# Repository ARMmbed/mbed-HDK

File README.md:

## This repository is not actively maintained anymore. For the latest updates, please visit: https://github.com/ARMmbed/mbed-HDK-Eagle-Projects

# mbed-HDK

The mbed Hardware Development Kit (mbed-HDK) is a collection of hardware design resources built on top of **Eagle PCB** that have been gathered to assist in the development of custom hardware benefiting from the mbed ecosystem, such as mbed OS, mbed SDK and associated technologies such as DAPLink. Working with development boards that were based on the mbed HDK is the most efficient way to get started with the mbed platform.

## Benefits of mbed-HDK

The mbed-HDK provides:

* Extensive collection of Eagle CAD parts libraries.
* Production Design Projects
	* Proven and manufactured mbed platforms for your reference complete with:
		* Eagle Schematic and Board files
		* PDF Schematic and Board copies
		* CAM Job GERBERS for manufacture (including pick/place and drill)
		* BOM (Bill of Materials)
* Bare Design Projects
	* Modular reference blocks of mbed TARGET and INTERFACE chip allowing rapid prototyping complete with:
		* Eagle Schematic and Board files
		* PDF Schematic copies

Please keep in mind that the resources are provided "as is". Though best efforts have been made to ensure the highest possible quality, no support or guarantees can be offered. The latest versions of Production Designs contained in the mbed HDK have been successfully manufactured by a third-party manufacturer and proven to work.

## Getting Started - Setup

The [User Guide](Docs/USER-GUIDE.md) will walk you through the setup to get the most out of the mbed-HDK.

## Getting Started - Your first PCB design
With the mbed-HDK the goal is to allow rapid PCB CAD prototyping for mbed designs, therefore we provide designs to get you started as quickly as possible. There are multiple ways to create your first design.
	
* Starting with a [Production Design Project](https://github.com/ARMmbed/mbed-HDK/tree/master/Production%20Design%20Projects/)
	* Choose this option if you wish to take an existing design that has been manufactured and tested as a starting point, or to make minor changes and then release yourself.

* Starting with a [Bare Design Project](Docs/DESIGN-GUIDE.md)
	* Choose this option if you wish to rapid prototype a design using modular blocks that have already been developed, these modular blocks include DAPLink INTERFACES and mbed TARGETS. For a simple guide to see how this works and how much time it will save.

* Starting with a blank Schematic and Board
	* Choose this option if you wish to utilise only the mbed-HDK tools in your design, this will still allow quick prototyping of mbed designs through using due to the provided mbed-hdk lbr, dru, ulp and CAM

## Moving On - Contributing your parts and designs

If you wish to contribute to the mbed HDK you can do so.

The [Contributors Guide](Docs/CONTRIBUTORS-GUIDE.md) details on how to contribute back to the mbed-HDK. There are 3 possible ways to contribute back to the mbed-HDK.

1. Contributing to mbed-HDK Eagle Libraries
2. Contributing to mbed-HDK Production Design Projects
3. Contributing to mbed-HDK Bare Design Projects

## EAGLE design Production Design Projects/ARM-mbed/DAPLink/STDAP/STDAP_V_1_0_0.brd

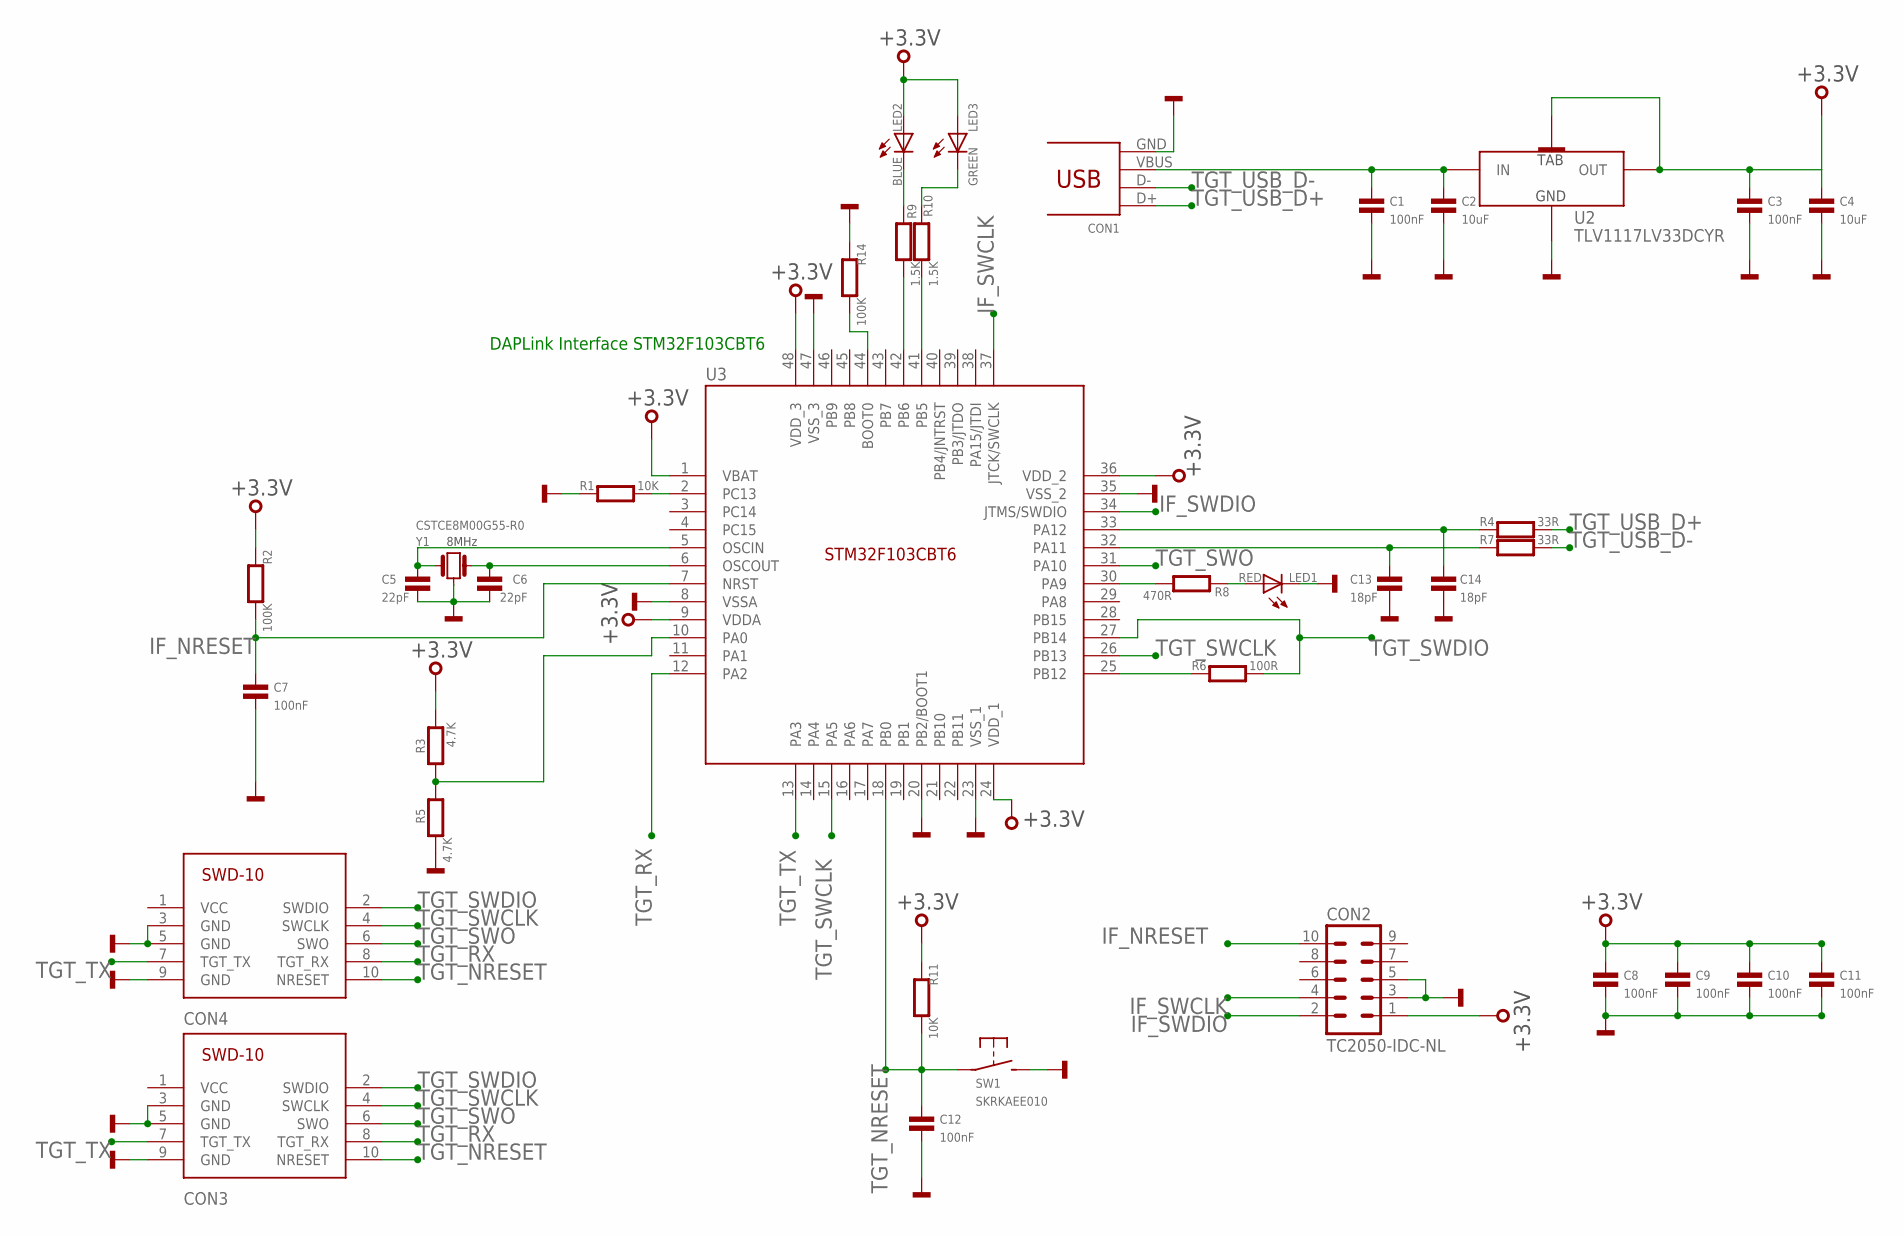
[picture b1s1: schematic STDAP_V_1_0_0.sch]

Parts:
C1, C3, C7, C8, C9, C10, C11, C12: 100nF; 0402
C2, C4: 10uF; 0603
C5, C6: 22pF; 0402
C13, C14: 18pF; 0402
CON1: 47346-0001; USB-MICRO-B-H
CON2: TC2050-IDC-NL
CON3: 3020-10-0200-00
CON4: 3220-10-0200-00
LED1: RED; CHIPLED_0603
LED2: BLUE; CHIPLED_0603
LED3: GREEN; CHIPLED_0603
R1, R11: 10K; 0402
R2, R14: 100K; 0402
R3, R5: 4.7K; 0402
R4, R7: 33R; 0402
R6: 100R; 0402
R8: 470R; 0402
R9, R10: 1.5K; 0402
SW1: SKRKAEE010
U2: TLV1117LV33DCYR; SOT223
U3: STM32F103CBT6; LQFP48
Y1: CSTCE8M00G55-R0

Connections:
+3.3V: C3.1, C4.1, C8.1, C9.1, C10.1, C11.1, CON2.1, LED2.A, LED3.A, R2.1, R3.1, R11.1, U2.OUT(1) (OUT), U2.OUT(2) (TAB), U3.1 (VBAT), U3.9 (VDDA), U3.24 (VDD_1), U3.36 (VDD_2), U3.48 (VDD_3)
GND: C1.2, C2.2, C3.2, C4.2, C5.2, C6.2, C7.2, C8.2, C9.2, C10.2, C11.2, C12.2, C13.2, C14.2, CON1.GND, CON2.3, CON2.5, CON3.3 (GND), CON3.5 (GND), CON3.9 (GND), CON4.3 (GND), CON4.5 (GND), CON4.9 (GND), LED1.C, R1.1, R5.2, R14.1, SW1.P$2 (S), U2.GND, U3.8 (VSSA), U3.20 (PB2/BOOT1), U3.23 (VSS_1), U3.35 (VSS_2), U3.47 (VSS_3), Y1.2
IF_NRESET: C7.1, CON2.10, R2.2, U3.7 (NRST)
IF_SWCLK: CON2.4, U3.37 (JTCK/SWCLK)
IF_SWDIO: CON2.2, U3.34 (JTMS/SWDIO)
unnamed: C1.1, C2.1, CON1.VBUS, U2.IN
unnamed: R8.2, U3.30 (PA9)
unnamed: R14.2, U3.44 (BOOT0)
unnamed: R1.2, U3.2 (PC13)
unnamed: C6.1, U3.6 (OSCOUT), Y1.3
unnamed: C5.1, U3.5 (OSCIN), Y1.1
unnamed: R3.2, R5.1, U3.10 (PA0)
unnamed: R9.2, U3.42 (PB6)
unnamed: R10.2, U3.41 (PB5)
unnamed: LED1.A, R8.1
unnamed: R6.1, U3.25 (PB12)
unnamed: LED2.C, R9.1
unnamed: LED3.C, R10.1
unnamed: C14.1, R4.1, U3.33 (PA12)
unnamed: C13.1, R7.1, U3.32 (PA11)
TGT_NRESET: C12.1, CON3.10 (NRESET), CON4.10 (NRESET), R11.2, SW1.P$1, U3.18 (PB0)
TGT_RX: CON3.8 (TGT_RX), CON4.8 (TGT_RX), U3.12 (PA2)
TGT_SWCLK: CON3.4 (SWCLK), CON4.4 (SWCLK), U3.15 (PA5), U3.26 (PB13)
TGT_SWDIO: CON3.2 (SWDIO), CON4.2 (SWDIO), R6.2, U3.27 (PB14)
TGT_SWO: CON3.6 (SWO), CON4.6 (SWO), U3.31 (PA10)
TGT_TX: CON3.7 (TGT_TX), CON4.7 (TGT_TX), U3.13 (PA3)
TGT_USB_D+: CON1.D+, R4.2
TGT_USB_D-: CON1.D-, R7.2

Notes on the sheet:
8MHz
DAPLink Interface STM32F103CBT6

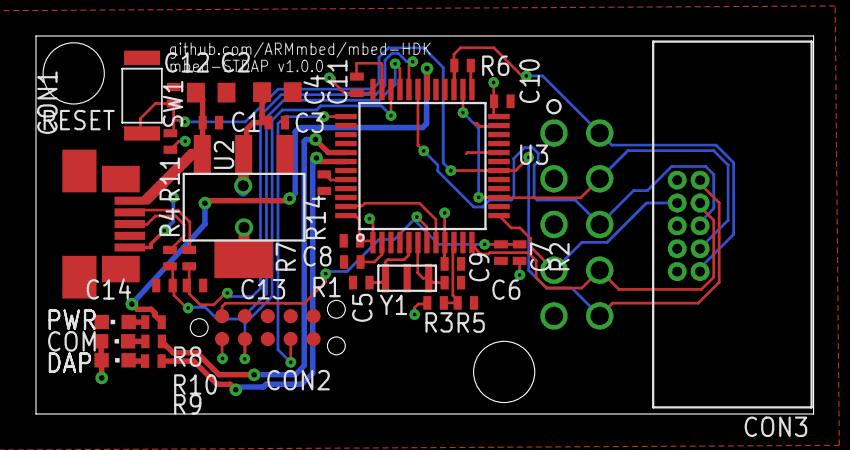
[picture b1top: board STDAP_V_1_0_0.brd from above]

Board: 2 copper layers, 43.2 x 21.0 mm, 37 parts (1 on the bottom side), 28 nets.

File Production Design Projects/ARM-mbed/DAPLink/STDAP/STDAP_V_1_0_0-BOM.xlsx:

Qty | Value | Device | Package | Parts | Description | MF | MFN | OC-DIGIKEY | OC-MOUSER | OC-NEWARK
1 | 3020-10-0200-00 | 3020-10-0200-00 | 3020-10-0200-00 | CON3 | 10 Positions Header Connector 0.100 (2.54mm) Through Hole | CNC Tech | 3020-10-0200-00 | 1175-1615-ND
1 | 3220-10-0200-00 | 3220-10-0200-00 | 3220-10-0200-00 | CON4 | 10 Positions Header Connector 0.050 (1.27mm) Through Hole | CNC Tech | 3220-10-0200-00 | 1175-1628-ND
2 | 1.5K | RESISTOR0402 | 402 | R9, R10 | Resistor | Panasonic | ERJ-2RKF1501X | P1.50KLCT-ND | 667-ERJ-2RKF1501X | 2302656
2 | 100K | RESISTOR0402 | 402 | R2, R14 | Resistor | Vishay | CRCW0402100KJNED | 541-100KJCT-ND | 71-CRCW0402J-100K-E3 | 1652738
1 | 100R | RESISTOR0402 | 402 | R6 | Resistor | Bourns | CR0402-JW-101GLF | CR0402-JW-101GLFCT-ND | 652-CR0402JW-101GLF | 32K2112
8 | 100nF | CAPACITOR0402 | 402 | C1, C3, C7, C8, C9, C10, C11, C12 | Capacitor | AVX | 0402YD104KAT2A | 478-1126-1-ND | 581-0402YD104K | 1327666
2 | 10K | RESISTOR0402 | 402 | R1, R11 | Resistor | Vishay | CRCW040210K0JNED | 541-10KJCT-ND | 71-CRCW0402J-10K-E3 | 59M6696
2 | 10uF | CAPACITOR0603 | 603 | C2, C4 | Capacitor | Yageo | CC0603MRX5R5BB106 | 311-1448-1-ND | 603-CC603MRX5R5BB106 | 1458902
2 | 18pF | CAPACITOR0402 | 402 | C13, C14 | Capacitor | Vishay | CRCW0402470RJNED | 541-470JCT-ND | 71-CRCW0402J-470-E3 | 59M6737
2 | 22pF | CAPACITOR0402 | 402 | C5, C6 | Capacitor | AVX | 04025A220JAT2A | 478-1074-1-ND | 581-04025A220J | 1327634
2 | 33R | RESISTOR0402 | 402 | R4, R7 | Resistor | Vishay | CRCW040233R0JNED | 541-33JCT-ND | 71-CRCW0402J-33-E3 | 72M6782
2 | 4.7K | RESISTOR0402 | 402 | R3, R5 | Resistor | Panasonic | ERJ-2RKF4701X | P4.70KLCT-ND | 667-ERJ-2RKF4701X | 64R5288
1 | 470R | RESISTOR0402 | 402 | R8 | Resistor | Vishay | CRCW0402470RJNED | 541-470JCT-ND | 71-CRCW0402J-470-E3 | 59M6737
1 | 47346-0001 | 47346-0001 | USB-MICRO-B-H | CON1 | USB Receptacle Horizontal Micro Type B | MOLEX | 47346-0001 |  | 538-47346-0001 | 1568026
1 | BLUE | SMD_LED0603 | CHIPLED_0603 | LED2 | LED SMD, Colour Blue | Wurth Electronics Inc | 150060BS75000 | 732-4966-1-ND | 710-150060BS75000 | 2322069
1 | CSTCE8M00G55-R0 | CSTCE8M00G55-R0 | CSTCE8M00G55-R0 | Y1 | Resonator Cermanic, Murata 8MHz 33pF | Murata | CSTCE8M00G55-R0 | 490-1195-1-ND | 81-CSTCE8M00G55-R0 | 2443270
1 | GREEN | SMD_LED0603 | CHIPLED_0603 | LED3 | LED SMD, Colour Green | Wurth Electronics Inc | 150060GS75000 | 732-4971-1-ND | 710-150060GS75000 | 2322070
1 | RED | SMD_LED0603 | CHIPLED_0603 | LED1 | LED SMD, Colour Red | Wurth Electronics Inc | 150060RS75000 | 732-4978-1-ND | 710-150060RS75000 | 2322071
1 | SKRKAEE010 | SKRKAEE010 | SKRKAEE010 | SW1 | MOMENTARY SWITCH PUSH VERTICAL (SPST) | ALPS | SKRKAEE010 |  | 688-SKRKAE
1 | STM32F103CBT6 | STM32F103CBT6 | LQFP48 | U3 | ARM¬Æ Cortex¬Æ-M3 STM32 F1 Microcontroller IC 32-Bit 72MHz 128KB (128K x 8) FLA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 | STMicroelectronics | STM32F103CBT6 | 497-6288-ND | 511-STM32F103CBT6 | 11N8296
1 | TLV1117LV33DCYR | TLV1117LV33DCYR | SOT223 | U2 | LDO Fixed Regulator 3.3v, 1A | Texas Instruments | TLV1117LV33DCYR | 296-28778-1-ND | 595-TLV1117LV33DCYR | 2323647

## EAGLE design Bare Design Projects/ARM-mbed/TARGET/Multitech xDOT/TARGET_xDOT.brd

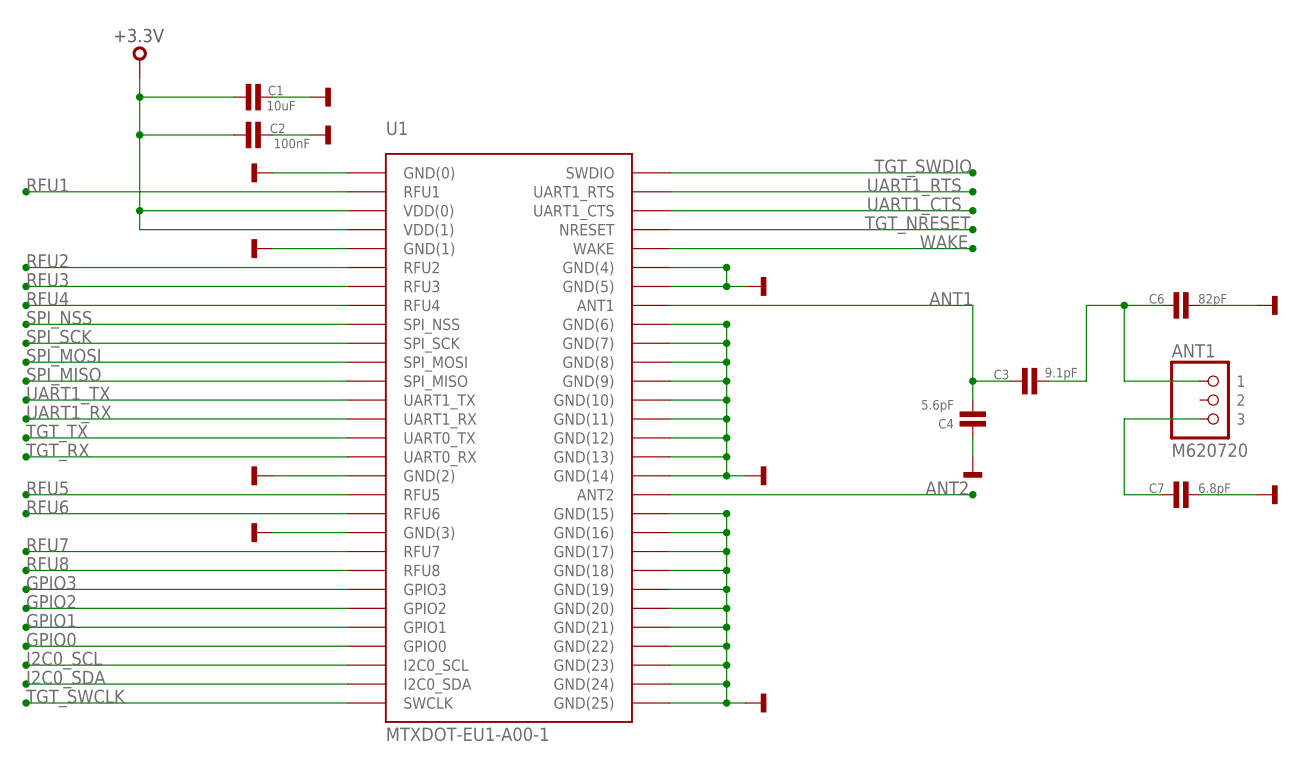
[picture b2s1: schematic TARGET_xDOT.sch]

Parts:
ANT1: M620720
C1: 10uF; 0603
C2: 100nF; 0603
C3: 9.1pF; 0402
C4: 5.6pF; 0402
C6: 82pF; 0402
C7: 6.8pF; 0402
U1: MTXDOT-EU1-A00-1; MTXDOT-EU1/NA1-A00-1

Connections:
+3.3V: C1.1, C2.1, U1.P$3 (VDD(0)), U1.P$4 (VDD(1))
ANT1: C3.1, C4.2, U1.P$37 (ANT1)
ANT2: U1.P$47 (ANT2)
GND: C1.2, C2.2, C4.1, C6.1, C7.1, U1.P$1 (GND(0)), U1.P$5 (GND(1)), U1.P$17 (GND(2)), U1.P$20 (GND(3)), U1.P$35 (GND(4)), U1.P$36 (GND(5)), U1.P$38 (GND(6)), U1.P$39 (GND(7)), U1.P$40 (GND(8)), U1.P$41 (GND(9)), U1.P$42 (GND(10)), U1.P$43 (GND(11)), U1.P$44 (GND(12)), U1.P$45 (GND(13)), U1.P$46 (GND(14)), U1.P$48 (GND(15)), U1.P$49 (GND(16)), U1.P$50 (GND(17)), U1.P$51 (GND(18)), U1.P$52 (GND(19)), U1.P$53 (GND(20)), U1.P$54 (GND(21)), U1.P$55 (GND(22)), U1.P$56 (GND(23)), U1.P$57 (GND(24)), U1.P$58 (GND(25))
GPIO0: U1.P$26 (GPIO0)
GPIO1: U1.P$25 (GPIO1)
GPIO2: U1.P$24 (GPIO2)
GPIO3: U1.P$23 (GPIO3)
I2C0_SCL: U1.P$27 (I2C0_SCL)
I2C0_SDA: U1.P$28 (I2C0_SDA)
unnamed: ANT1.P$3 (3), C7.2
unnamed: ANT1.P$1 (1), C3.2, C6.2
RFU1: U1.P$2 (RFU1)
RFU2: U1.P$6 (RFU2)
RFU3: U1.P$7 (RFU3)
RFU4: U1.P$8 (RFU4)
RFU5: U1.P$18 (RFU5)
RFU6: U1.P$19 (RFU6)
RFU7: U1.P$21 (RFU7)
RFU8: U1.P$22 (RFU8)
SPI_MISO: U1.P$12 (SPI_MISO)
SPI_MOSI: U1.P$11 (SPI_MOSI)
SPI_NSS: U1.P$9 (SPI_NSS)
SPI_SCK: U1.P$10 (SPI_SCK)
TGT_NRESET: U1.P$33 (NRESET)
TGT_RX: U1.P$16 (UART0_RX)
TGT_SWCLK: U1.P$29 (SWCLK)
TGT_SWDIO: U1.P$30 (SWDIO)
TGT_TX: U1.P$15 (UART0_TX)
UART1_CTS: U1.P$32 (UART1_CTS)
UART1_RTS: U1.P$31 (UART1_RTS)
UART1_RX: U1.P$14 (UART1_RX)
UART1_TX: U1.P$13 (UART1_TX)
WAKE: U1.P$34 (WAKE)

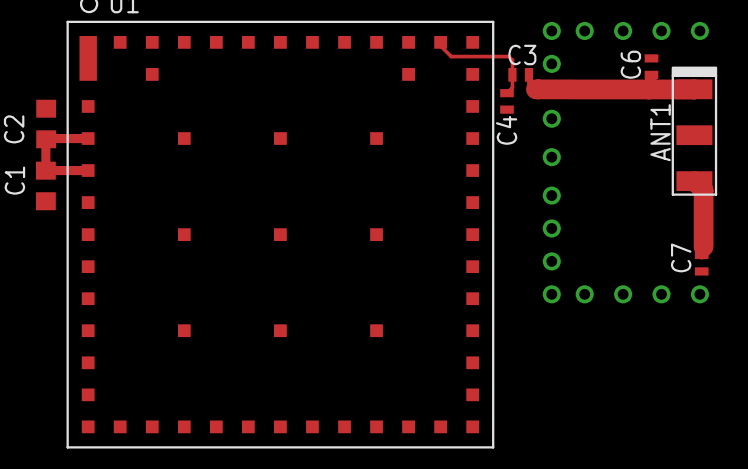
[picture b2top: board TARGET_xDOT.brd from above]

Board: 2 copper layers, 8 parts (0 on the bottom side), 5 nets.

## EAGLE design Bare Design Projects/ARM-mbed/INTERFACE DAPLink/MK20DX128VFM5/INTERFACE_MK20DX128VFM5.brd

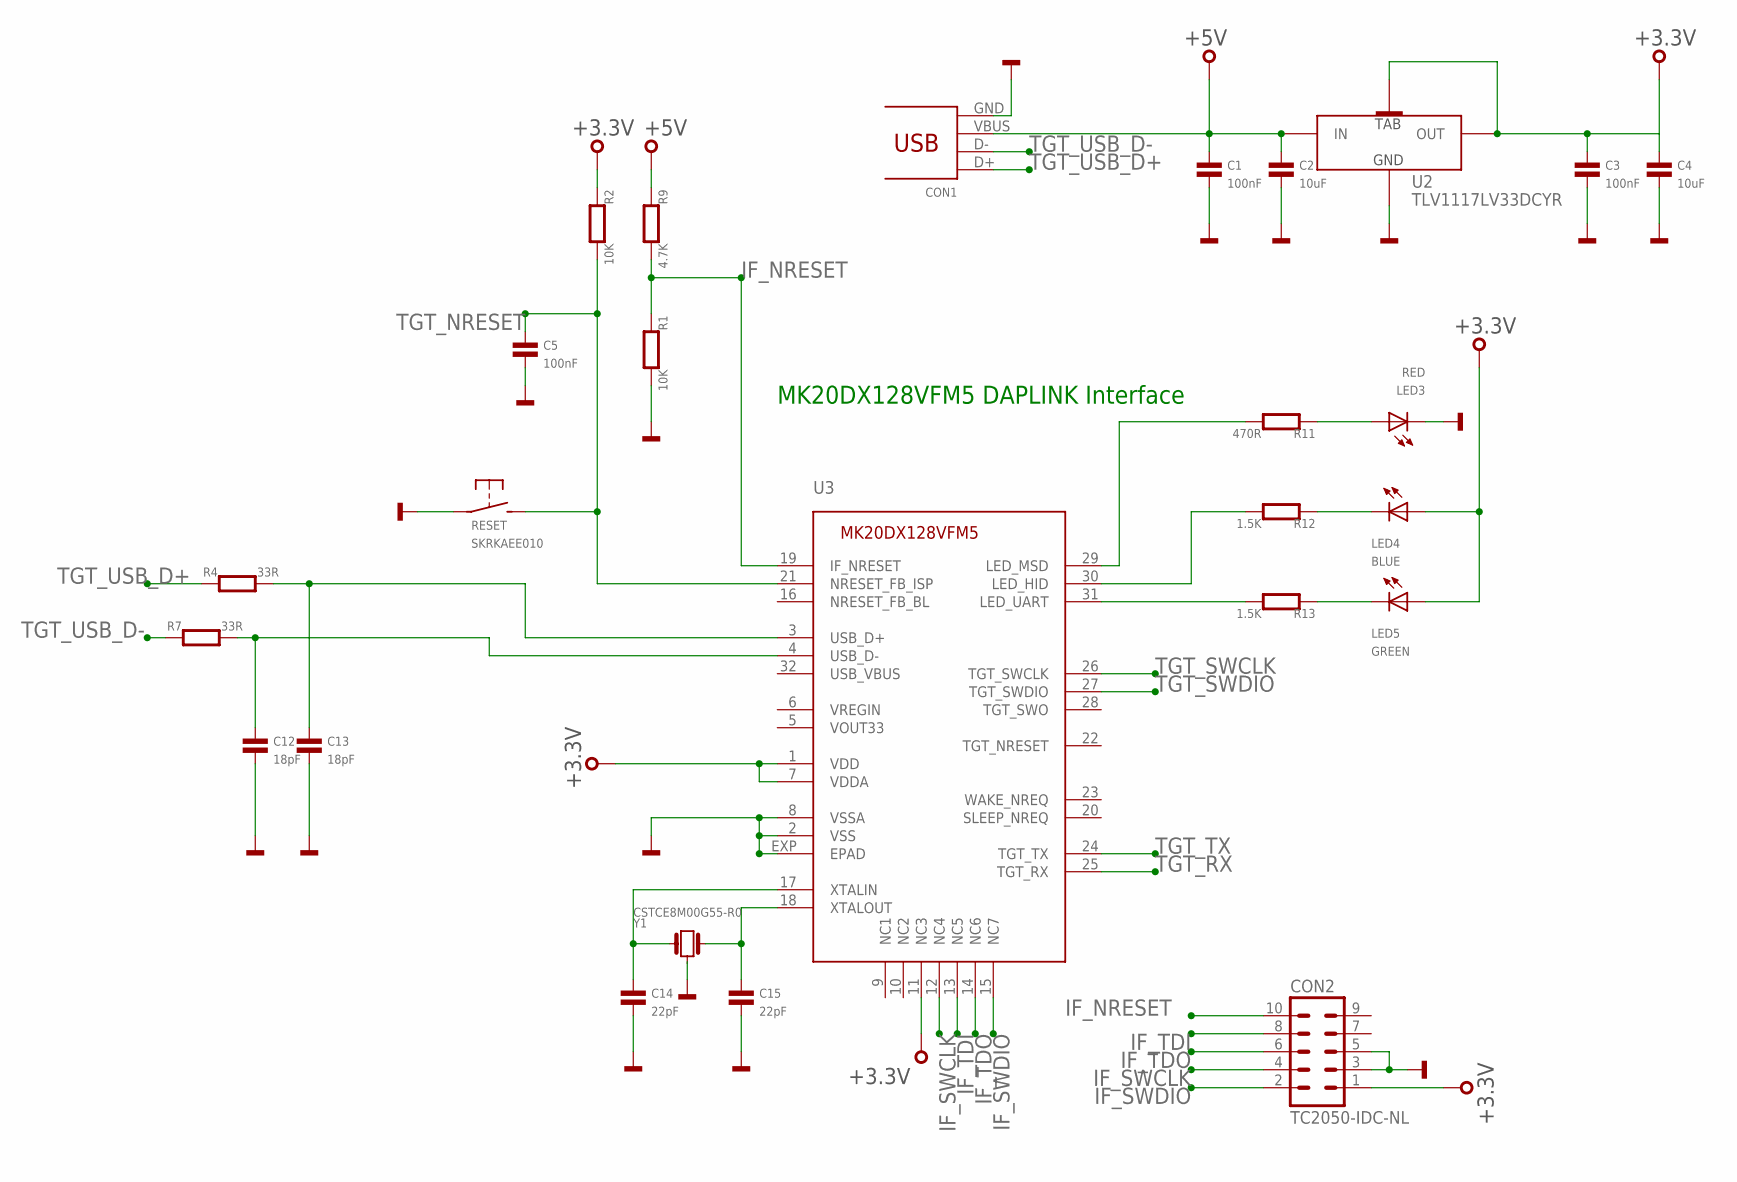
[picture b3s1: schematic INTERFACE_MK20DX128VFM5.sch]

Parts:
C1, C3, C5: 100nF; 0402
C2, C4: 10uF; 0603
C12, C13: 18pF; 0402
C14, C15: 22pF; 0402
CON1: 47346-0001; USB-MICRO-B-H
CON2: TC2050-IDC-NL
LED3: RED; CHIPLED_0603
LED4: BLUE; CHIPLED_0603
LED5: GREEN; CHIPLED_0603
R1, R2: 10K; 0402
R4, R7: 33R; 0402
R9: 4.7K; 0402
R11: 470R; 0402
R12, R13: 1.5K; 0402
RESET: SKRKAEE010
U2: TLV1117LV33DCYR; SOT223
U3: IF_MK20DX128VFM5; HVQFN33
Y1: CSTCE8M00G55-R0

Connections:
+3.3V: C3.1, C4.1, CON2.1, LED4.A, LED5.A, R2.1, U2.OUT(1) (OUT), U2.OUT(2) (TAB), U3.1 (VDD), U3.7 (VDDA), U3.11 (NC3)
+5V: C1.1, C2.1, CON1.VBUS, R9.1, U2.IN
GND: C1.2, C2.2, C3.2, C4.2, C5.2, C12.2, C13.2, C14.2, C15.2, CON1.GND, CON2.3, CON2.5, LED3.C, R1.2, RESET.P$1, U2.GND, U3.2 (VSS), U3.8 (VSSA), U3.EXP (EPAD), Y1.2
HID: R12.2, U3.30 (LED_HID)
IF_NRESET: CON2.10, R1.1, R9.2, U3.19 (IF_NRESET)
IF_SWCLK: CON2.4, U3.12 (NC4)
IF_SWDIO: CON2.2, U3.15 (NC7)
IF_TDI: CON2.8, U3.13 (NC5)
IF_TDO: CON2.6, U3.14 (NC6)
MSD: R11.2, U3.29 (LED_MSD)
unnamed: LED3.A, R11.1
unnamed: C13.1, R4.2, U3.3 (USB_D+)
unnamed: C12.1, R7.2, U3.4 (USB_D-)
unnamed: LED4.C, R12.1
unnamed: LED5.C, R13.1
unnamed: C15.1, U3.18 (XTALOUT), Y1.3
unnamed: C14.1, U3.17 (XTALIN), Y1.1
TGT_NRESET: C5.1, R2.2, RESET.P$2 (S), U3.21 (NRESET_FB_ISP)
TGT_RX: U3.25 (TGT_RX)
TGT_SWCLK: U3.26 (TGT_SWCLK)
TGT_SWDIO: U3.27 (TGT_SWDIO)
TGT_TX: U3.24 (TGT_TX)
TGT_USB_D+: CON1.D+, R4.1
TGT_USB_D-: CON1.D-, R7.1
UART: R13.2, U3.31 (LED_UART)

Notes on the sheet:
MK20DX128VFM5 DAPLINK Interface

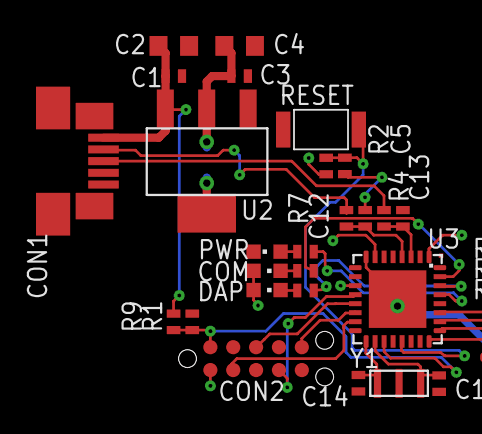
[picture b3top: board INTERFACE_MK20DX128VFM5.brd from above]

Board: 2 copper layers, 26 parts (0 on the bottom side), 21 nets.

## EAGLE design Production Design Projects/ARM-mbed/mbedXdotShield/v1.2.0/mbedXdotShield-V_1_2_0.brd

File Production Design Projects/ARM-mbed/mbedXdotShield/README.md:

## mbedXdotShield

The mbed xDOT shield features a Multitech xDOT LORA module, with mbed compatabile drag-drop programming. This device is both a independent platform or can act as a shield to make any device send or recieve LORA data via UART.

## Whats included here?

* Eagle Schematic and Board files
* PDF Schematic and Board copies
* CAM Job GERBERS for manufacture (including pick/place and drill)
* BOM (Bill of Materials)
* eBOM (An online BOM for easy purchasing!)

The design features:

        1. Multitech xDOT module: ST ARM® Cortex® M3 processor (STM32L151CCU6)
        2. DAPLink Interface LPC11u35: Drag Drop programming
        3. 868/915MHz LoRa chip antenna
        4. AT45DB161E-SSHD-T Serial Flash
        5. 3V JST-PH Battery connector
        6. Arduino style headers: Allowing device to operate as LoRa shield
        7. UART swap: Slide switch, allowing UART TX/RX to be swapped, if using as shield switch to 'On'

## Hardware

The hardware design files can be found in this repo as part of the mbed HDK and are referenced by their most up-to-date version v’x.x.x’.(If you wish to find an older project version, navigate to releases or checkout a previous commit).

## Software and more info

The software for tests and more info can be found in the [CI Test Shield github repository](http://www.github.com/armmbed/ci-test-shield). 

## How to get hardware

1. Buy pre-assembled board from vendor (todo)
2. Do it yourself

## Revisions
- **v 1.2.0** (23/06/17)
	-  'D2' Replaced with 'R29' 0ohm.
	-  mbed enabled logo on silkscreen
	-  Modified 'CON2' now recommended voltage is 4.5V (from 3V) for VBAT, rerouted to input of LDO 'U2'
- **v 1.1.0** (01/06/17)
	- 	'R3':1.5K->220R
	-  'R13','R14':470R->1.5K
	-  Placed resistors 'R14'-to-'R27' on front of PCB (no components on rear)
	-  Rerouted UART1TX, UART1RX (improved antenna performance)
	-  Moved USB micro further into board
- **v 1.0.0** (18/05/17)
 - Initial Commit

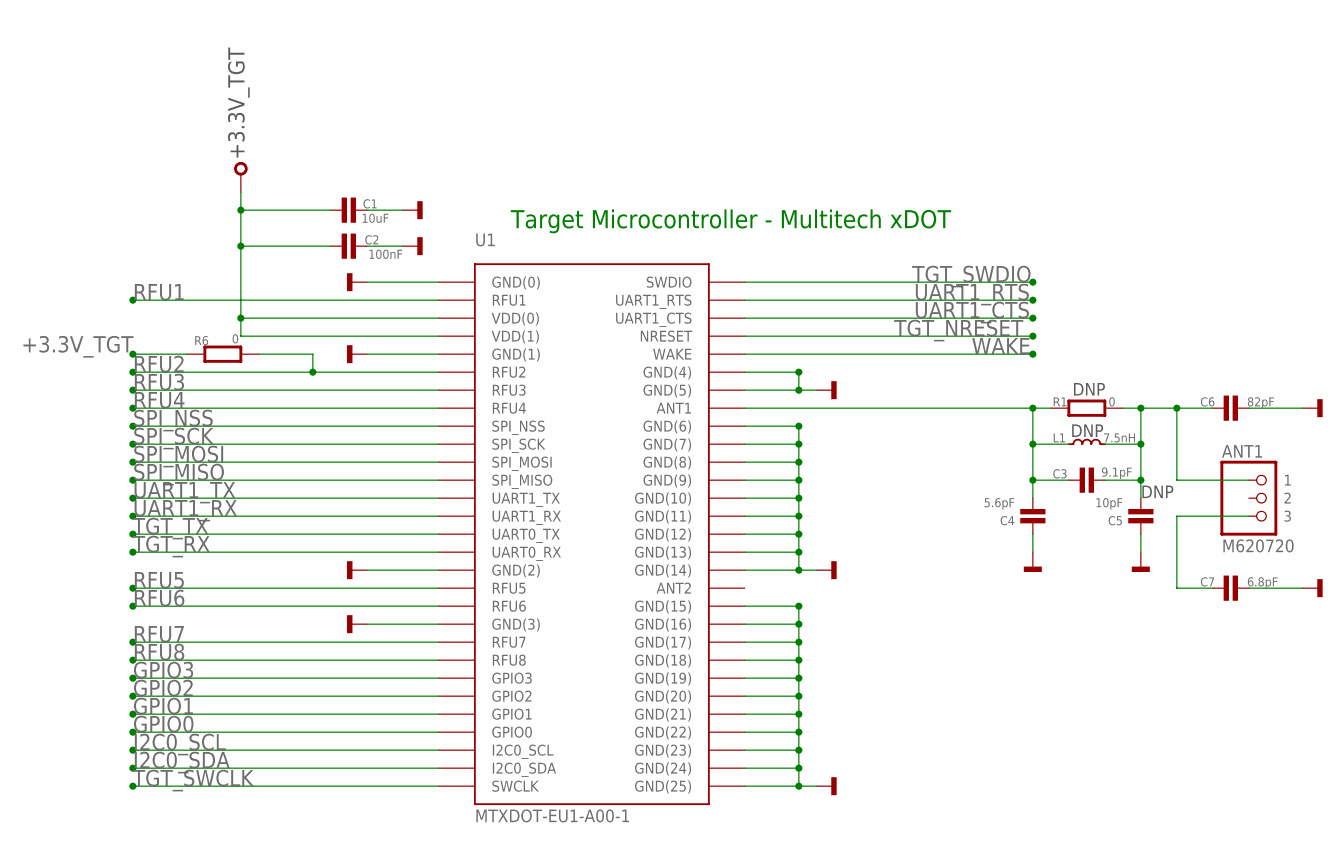
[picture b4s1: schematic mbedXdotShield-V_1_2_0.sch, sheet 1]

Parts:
ANT1: M620720
C1: 10uF; 0603
C2: 100nF; 0603
C3: 9.1pF; 0402
C4: 5.6pF; 0402
C5: 10pF; 0402
C6: 82pF; 0402
C7: 6.8pF; 0402
L1: 7.5nH; 0402
R1, R6: 0; 0402
U1: MTXDOT-EU1-A00-1; MTXDOT-EU1/NA1-A00-1

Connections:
+3.3V_TGT: C1.1, C2.1, R6.1, U1.P$3 (VDD(0)), U1.P$4 (VDD(1)); also elsewhere on the board
ANT1: C3.1, C4.2, L1.1, R1.1, U1.P$37 (ANT1)
GND: C1.2, C2.2, C4.1, C5.1, C6.1, C7.1, U1.P$1 (GND(0)), U1.P$5 (GND(1)), U1.P$17 (GND(2)), U1.P$20 (GND(3)), U1.P$35 (GND(4)), U1.P$36 (GND(5)), U1.P$38 (GND(6)), U1.P$39 (GND(7)), U1.P$40 (GND(8)), U1.P$41 (GND(9)), U1.P$42 (GND(10)), U1.P$43 (GND(11)), U1.P$44 (GND(12)), U1.P$45 (GND(13)), U1.P$46 (GND(14)), U1.P$48 (GND(15)), U1.P$49 (GND(16)), U1.P$50 (GND(17)), U1.P$51 (GND(18)), U1.P$52 (GND(19)), U1.P$53 (GND(20)), U1.P$54 (GND(21)), U1.P$55 (GND(22)), U1.P$56 (GND(23)), U1.P$57 (GND(24)), U1.P$58 (GND(25)); also elsewhere on the board
GPIO0: U1.P$26 (GPIO0); also elsewhere on the board
GPIO1: U1.P$25 (GPIO1); also elsewhere on the board
GPIO2: U1.P$24 (GPIO2); also elsewhere on the board
GPIO3: U1.P$23 (GPIO3); also elsewhere on the board
I2C0_SCL: U1.P$27 (I2C0_SCL); also elsewhere on the board
I2C0_SDA: U1.P$28 (I2C0_SDA); also elsewhere on the board
unnamed: ANT1.P$3 (3), C7.2
unnamed: ANT1.P$1 (1), C3.2, C5.2, C6.2, L1.2, R1.2
RFU1: U1.P$2 (RFU1)
RFU2: R6.2, U1.P$6 (RFU2)
RFU3: U1.P$7 (RFU3)
RFU4: U1.P$8 (RFU4)
RFU5: U1.P$18 (RFU5)
RFU6: U1.P$19 (RFU6)
RFU7: U1.P$21 (RFU7)
RFU8: U1.P$22 (RFU8)
SPI_MISO: U1.P$12 (SPI_MISO); also elsewhere on the board
SPI_MOSI: U1.P$11 (SPI_MOSI); also elsewhere on the board
SPI_NSS: U1.P$9 (SPI_NSS); also elsewhere on the board
SPI_SCK: U1.P$10 (SPI_SCK); also elsewhere on the board
TGT_NRESET: U1.P$33 (NRESET); also elsewhere on the board
TGT_RX: U1.P$16 (UART0_RX); also elsewhere on the board
TGT_SWCLK: U1.P$29 (SWCLK); also elsewhere on the board
TGT_SWDIO: U1.P$30 (SWDIO); also elsewhere on the board
TGT_TX: U1.P$15 (UART0_TX); also elsewhere on the board
UART1_CTS: U1.P$32 (UART1_CTS); also elsewhere on the board
UART1_RTS: U1.P$31 (UART1_RTS); also elsewhere on the board
UART1_RX: U1.P$14 (UART1_RX); also elsewhere on the board
UART1_TX: U1.P$13 (UART1_TX); also elsewhere on the board
WAKE: U1.P$34 (WAKE); also elsewhere on the board

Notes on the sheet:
Target Microcontroller - Multitech xDOT
DNP

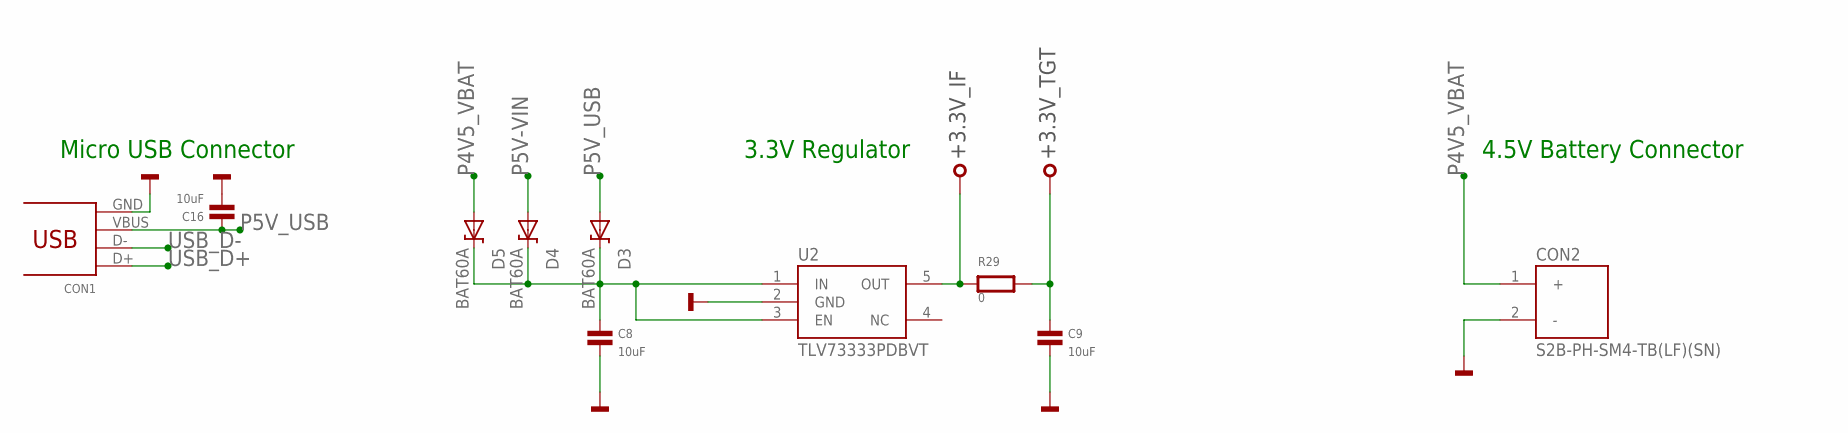
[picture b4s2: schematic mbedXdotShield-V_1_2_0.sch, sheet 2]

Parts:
C8, C9, C16: 10uF; 0603
CON1: 47346-0001; USB-MICRO-B-H
CON2: S2B-PH-SM4-TB(LF)(SN)
D3, D4, D5: BAT60A; SOD323
R29: 0; 0805
U2: TLV73333PDBVT; SOT23-5

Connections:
+3.3V_IF: R29.1, U2.5 (OUT); also elsewhere on the board
+3.3V_TGT: C9.1, R29.2; also elsewhere on the board
GND: C8.2, C9.2, C16.2, CON1.GND, CON2.2 (-), U2.2 (GND); also elsewhere on the board
unnamed: C8.1, D3.K, D4.K, D5.K, U2.1 (IN), U2.3 (EN)
P4V5_VBAT: CON2.1 (+), D5.A
P5V-VIN: D4.A; also elsewhere on the board
P5V_USB: C16.1, CON1.VBUS, D3.A; also elsewhere on the board
USB_D+: CON1.D+; also elsewhere on the board
USB_D-: CON1.D-; also elsewhere on the board

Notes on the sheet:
3.3V Regulator
Micro USB Connector
4.5V Battery Connector

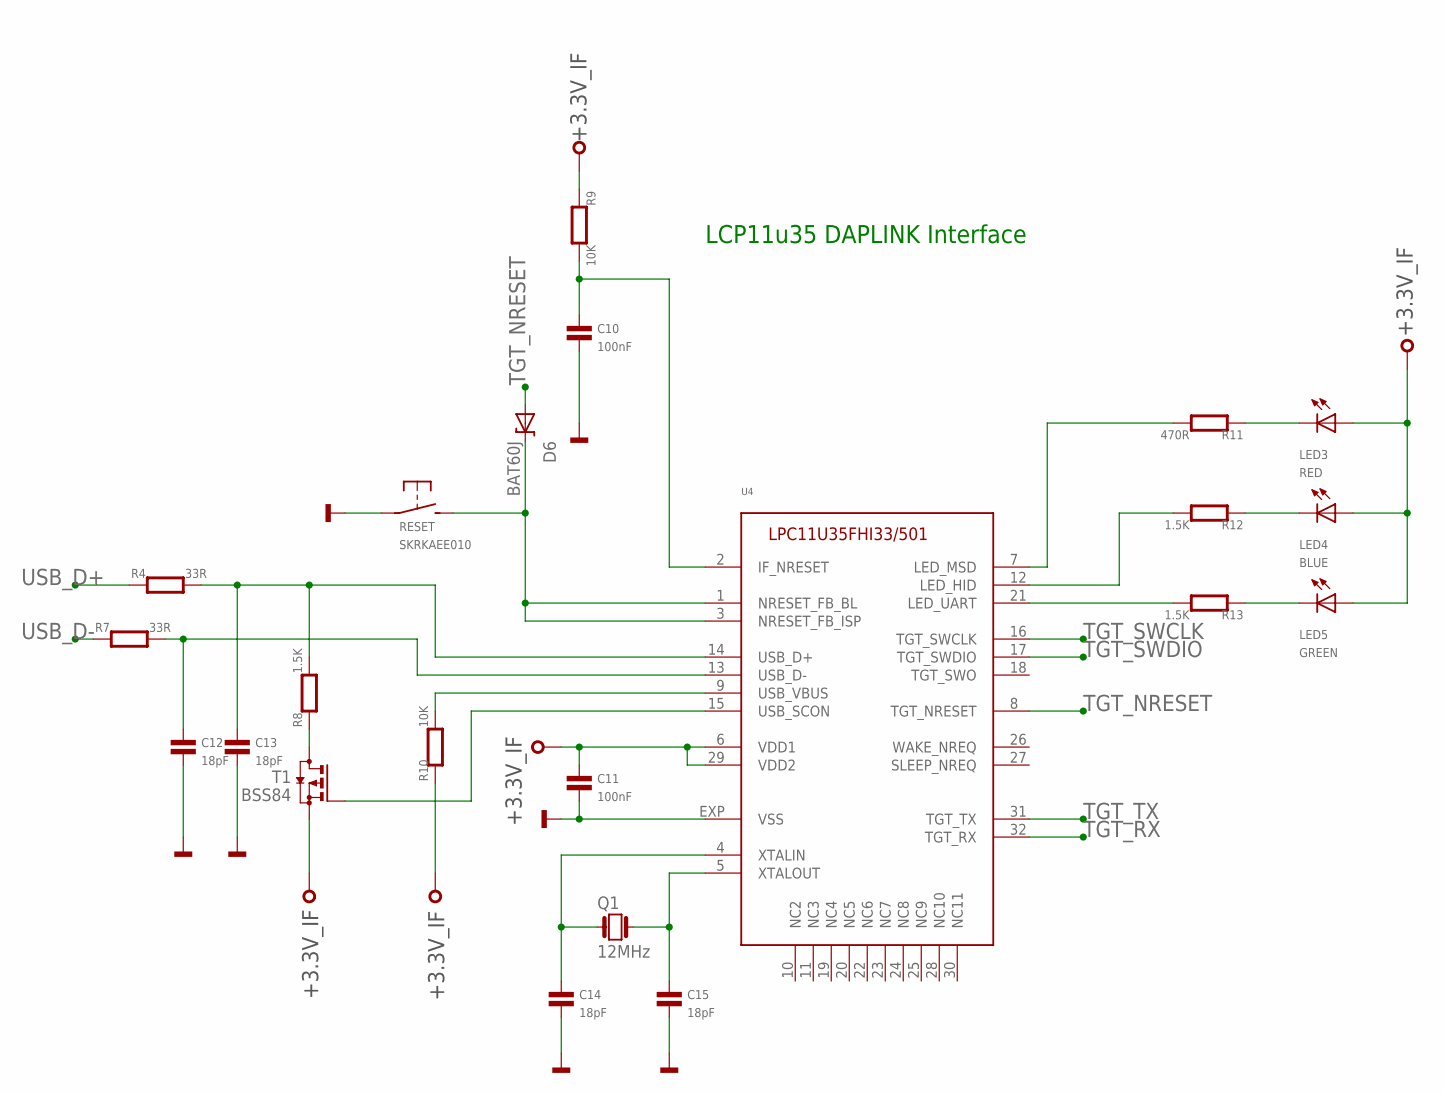
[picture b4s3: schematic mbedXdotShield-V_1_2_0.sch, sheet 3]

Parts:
C10, C11: 100nF; 0402
C12, C13, C14, C15: 18pF; 0402
D6: BAT60J; SOD323
LED3: RED; CHIPLED_0603
LED4: BLUE; CHIPLED_0603
LED5: GREEN; CHIPLED_0603
Q1: 12MHz; 3.2X.2.5
R4, R7: 33R; 0402
R8, R12, R13: 1.5K; 0402
R9, R10: 10K; 0402
R11: 470R; 0402
RESET: SKRKAEE010
T1: BSS84; SOT23-3
U4: IF-LPC11U35; HVQFN33

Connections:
+3.3V_IF: C11.1, LED3.A, LED4.A, LED5.A, R9.1, R10.1, T1.2 (S), U4.6 (VDD1), U4.29 (VDD2); also elsewhere on the board
GND: C10.2, C11.2, C12.2, C13.2, C14.2, C15.2, RESET.P$1, U4.EXP (VSS); also elsewhere on the board
HID: R12.2, U4.12 (LED_HID)
IF_NRESET: C10.1, R9.2, U4.2 (IF_NRESET)
ISP: D6.K, RESET.P$2 (S), U4.1 (NRESET_FB_BL), U4.3 (NRESET_FB_ISP)
MSD: R11.2, U4.7 (LED_MSD)
unnamed: C13.1, R4.2, R8.2, U4.14 (USB_D+)
unnamed: C12.1, R7.2, U4.13 (USB_D-)
unnamed: T1.1 (G), U4.15 (USB_SCON)
unnamed: R8.1, T1.3 (D)
unnamed: R10.2, U4.9 (USB_VBUS)
unnamed: LED3.C, R11.1
unnamed: LED4.C, R12.1
unnamed: LED5.C, R13.1
unnamed: C15.1, Q1.P$3 (2), U4.5 (XTALOUT)
unnamed: C14.1, Q1.P$1 (1), U4.4 (XTALIN)
TGT_NRESET: D6.A, U4.8 (TGT_NRESET); also elsewhere on the board
TGT_RX: U4.32 (TGT_RX); also elsewhere on the board
TGT_SWCLK: U4.16 (TGT_SWCLK); also elsewhere on the board
TGT_SWDIO: U4.17 (TGT_SWDIO); also elsewhere on the board
TGT_TX: U4.31 (TGT_TX); also elsewhere on the board
UART: R13.2, U4.21 (LED_UART)
USB_D+: R4.1; also elsewhere on the board
USB_D-: R7.1; also elsewhere on the board

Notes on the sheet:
LCP11u35 DAPLINK Interface

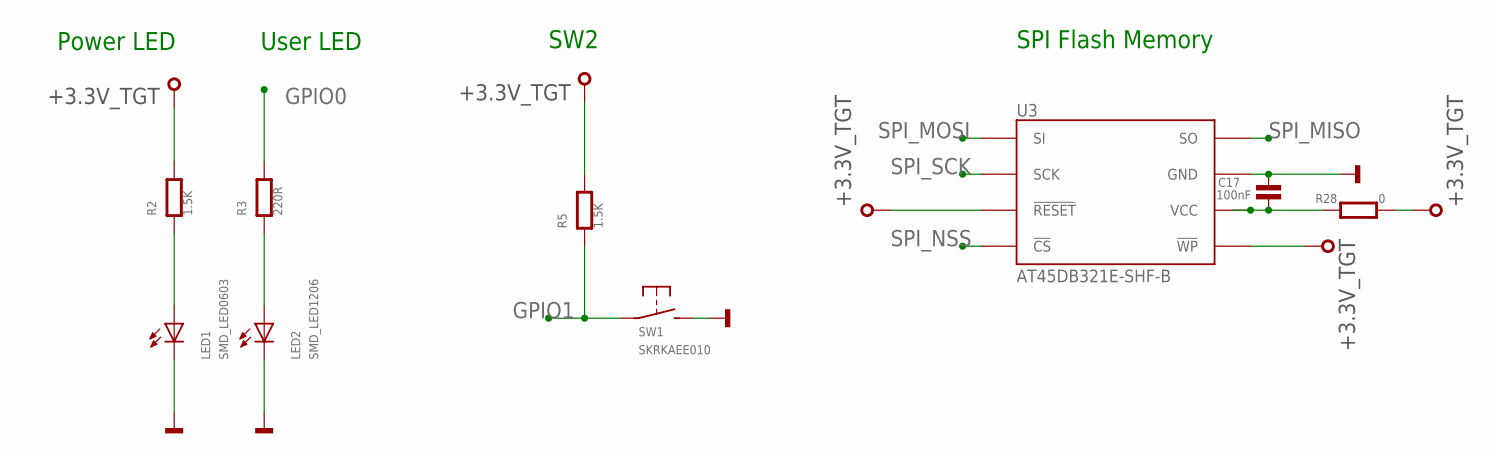
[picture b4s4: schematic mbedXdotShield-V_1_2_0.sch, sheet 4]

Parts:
C17: 100nF; 0603
LED1: SMD_LED0603; CHIPLED_0603
LED2: SMD_LED1206; CHIPLED_1206
R2, R5: 1.5K; 0402
R3: 220R; 0402
R28: 0; 0402
SW1: SKRKAEE010
U3: AT45DB321E-SHF-B; SO8

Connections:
+3.3V_TGT: R2.2, R5.2, R28.2, U3.3 (!RESET), U3.5 (!WP); also elsewhere on the board
GND: C17.1, LED1.C, LED2.C, SW1.P$2 (S), U3.7 (GND); also elsewhere on the board
GPIO0: R3.2; also elsewhere on the board
GPIO1: R5.1, SW1.P$1; also elsewhere on the board
unnamed: LED2.A, R3.1
unnamed: LED1.A, R2.1
unnamed: C17.2, R28.1, U3.6 (VCC)
SPI_MISO: U3.8 (SO); also elsewhere on the board
SPI_MOSI: U3.1 (SI); also elsewhere on the board
SPI_NSS: U3.4 (!CS); also elsewhere on the board
SPI_SCK: U3.2 (SCK); also elsewhere on the board

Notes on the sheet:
SW2
Power LED
User LED
SPI Flash Memory

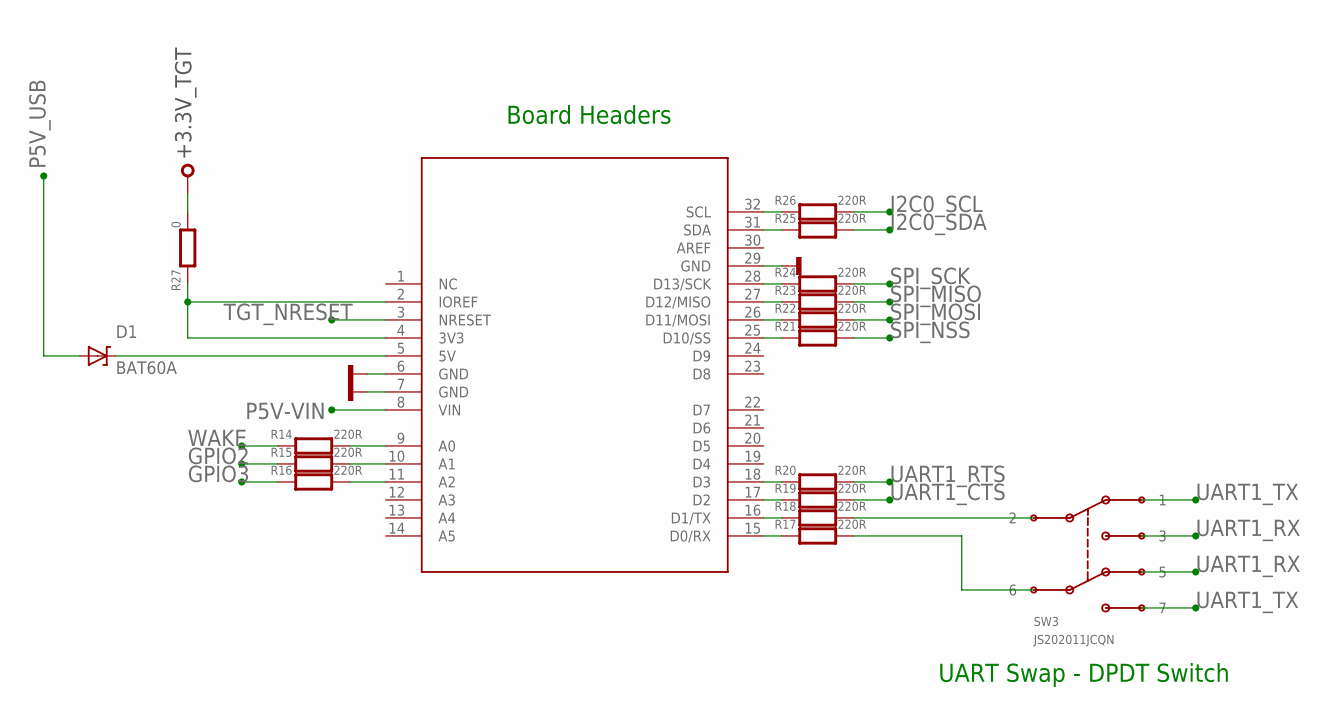
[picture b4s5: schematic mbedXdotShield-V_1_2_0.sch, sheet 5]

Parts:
BRD1: K64F/K22F-SHIELD; K64F/K22F
D1: BAT60A; SOD323
R14, R15, R16, R17, R18, R19, R20, R21, R22, R23, R24, R25, R26: 220R; 0402
R27: 0; 0402
SW3: JS202011JCQN

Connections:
+3.3V_TGT: R27.2; also elsewhere on the board
GND: BRD1.6 (GND), BRD1.7 (GND), BRD1.29 (GND); also elsewhere on the board
GPIO2: R15.1; also elsewhere on the board
GPIO3: R16.1; also elsewhere on the board
I2C0_SCL: R26.2; also elsewhere on the board
I2C0_SDA: R25.2; also elsewhere on the board
unnamed: BRD1.9 (A0), R14.2
unnamed: BRD1.10 (A1), R15.2
unnamed: BRD1.11 (A2), R16.2
unnamed: BRD1.15 (D0/RX), R17.1
unnamed: BRD1.16 (D1/TX), R18.1
unnamed: BRD1.17 (D2), R19.1
unnamed: BRD1.5 (5V), D1.K
unnamed: BRD1.18 (D3), R20.1
unnamed: BRD1.25 (D10/SS), R21.1
unnamed: BRD1.26 (D11/MOSI), R22.1
unnamed: BRD1.27 (D12/MISO), R23.1
unnamed: BRD1.28 (D13/SCK), R24.1
unnamed: BRD1.31 (SDA), R25.1
unnamed: BRD1.32 (SCL), R26.1
unnamed: BRD1.2 (IOREF), BRD1.4 (3V3), R27.1
unnamed: R17.2, SW3.6
unnamed: R18.2, SW3.2
P5V-VIN: BRD1.8 (VIN); also elsewhere on the board
P5V_USB: D1.A; also elsewhere on the board
SPI_MISO: R23.2; also elsewhere on the board
SPI_MOSI: R22.2; also elsewhere on the board
SPI_NSS: R21.2; also elsewhere on the board
SPI_SCK: R24.2; also elsewhere on the board
TGT_NRESET: BRD1.3 (NRESET); also elsewhere on the board
UART1_CTS: R19.2; also elsewhere on the board
UART1_RTS: R20.2; also elsewhere on the board
UART1_RX: SW3.3, SW3.5; also elsewhere on the board
UART1_TX: SW3.1, SW3.7; also elsewhere on the board
WAKE: R14.1; also elsewhere on the board

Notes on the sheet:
Board Headers
UART Swap - DPDT Switch
